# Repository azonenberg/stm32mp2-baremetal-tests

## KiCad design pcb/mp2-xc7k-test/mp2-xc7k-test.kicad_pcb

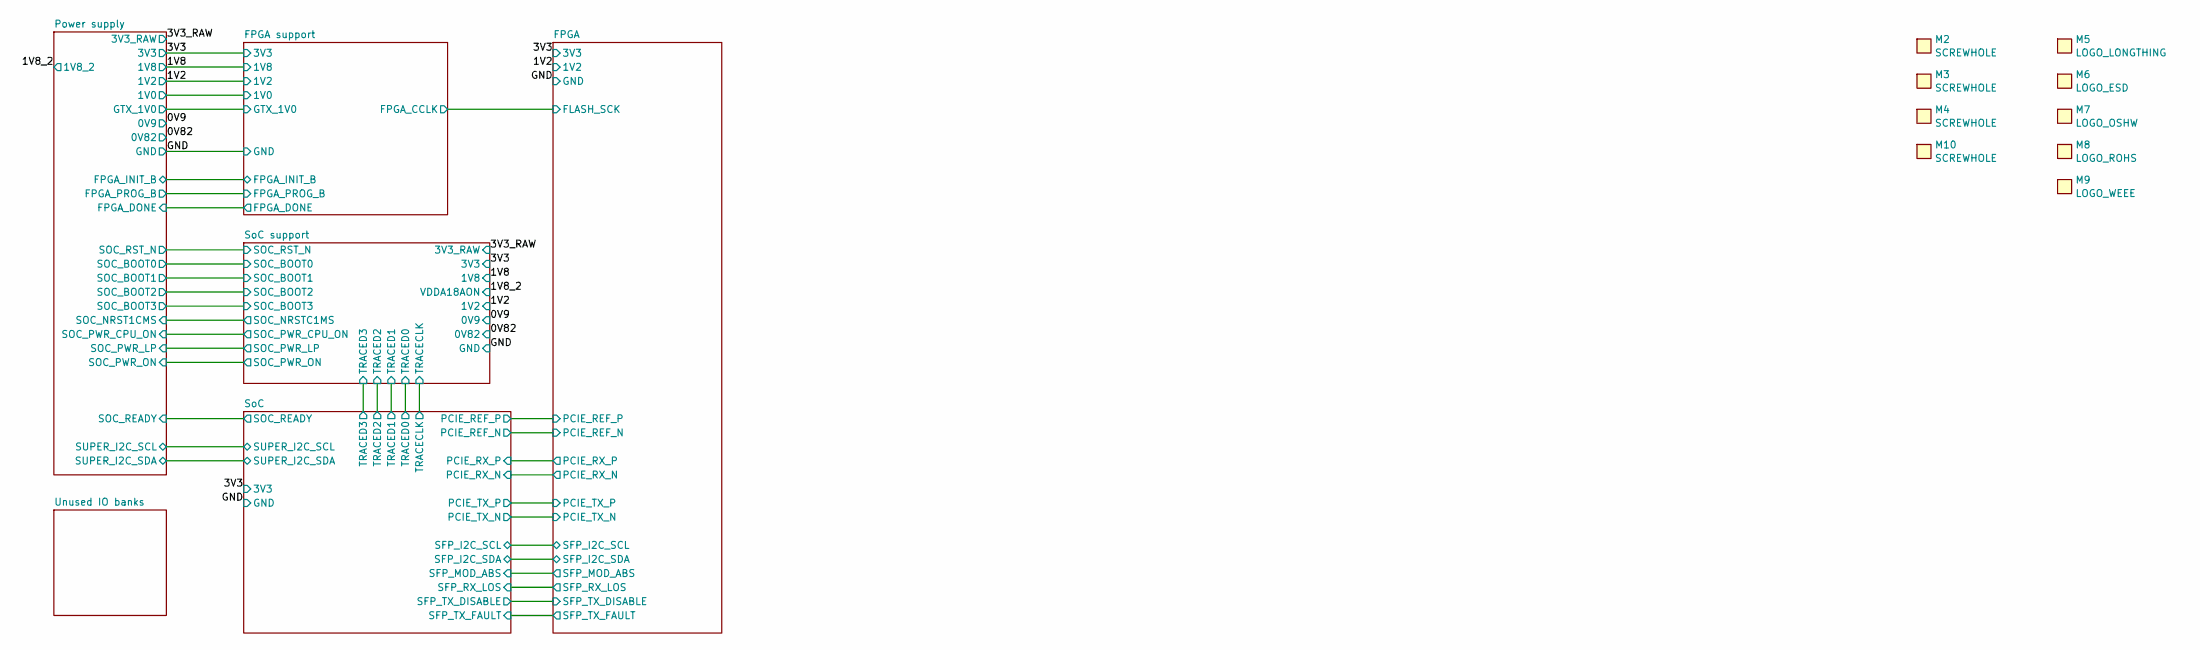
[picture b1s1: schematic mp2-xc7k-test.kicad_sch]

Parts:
M2, M3, M4, M10: SCREWHOLE; MECHANICAL_CLEARANCEHOLE_4_40
M5: LOGO_LONGTHING; LONGTHING-1200DPI
M6: LOGO_ESD; LOGO_ESD_SENSITIVE_7MM
M7: LOGO_OSHW; Logo_silk_OSHW_6x6mm
M8: LOGO_ROHS; Logo_silk_ROHS_5x2.8mm
M9: LOGO_WEEE; Logo_silk_WEEE_3.4x5mm

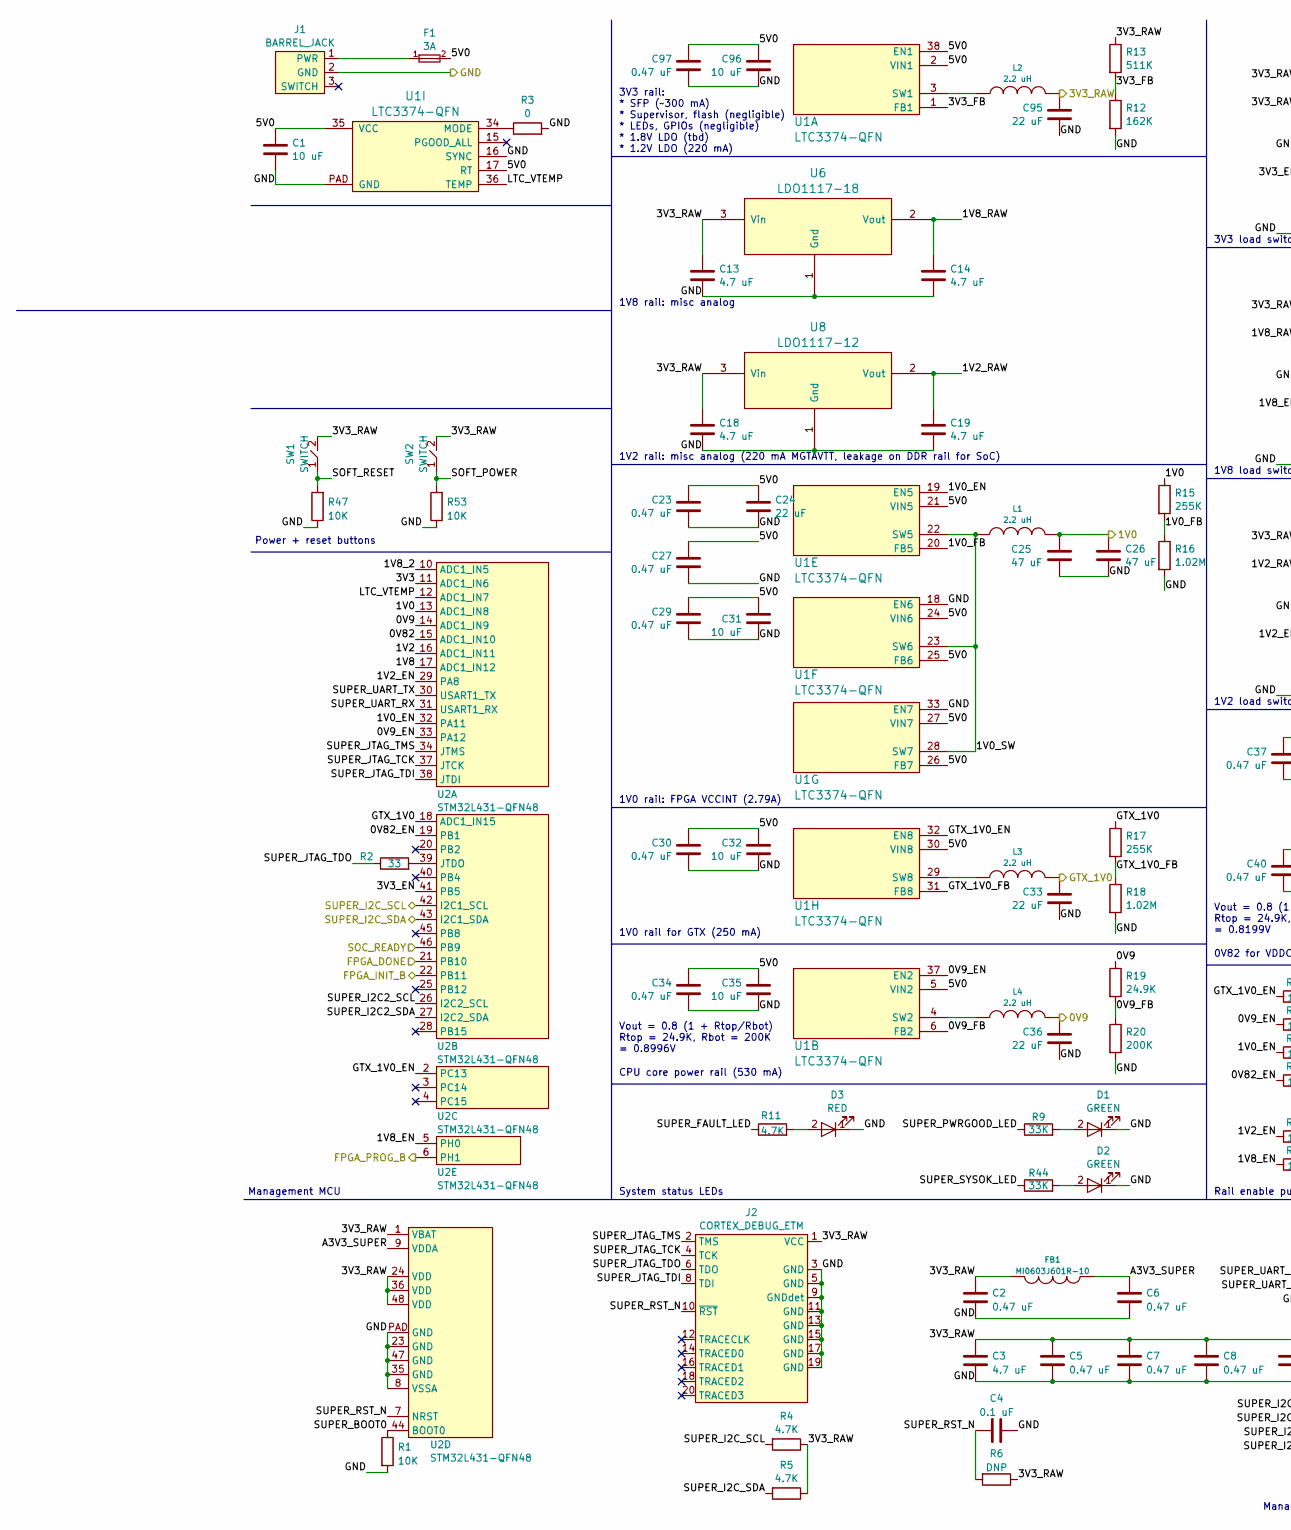
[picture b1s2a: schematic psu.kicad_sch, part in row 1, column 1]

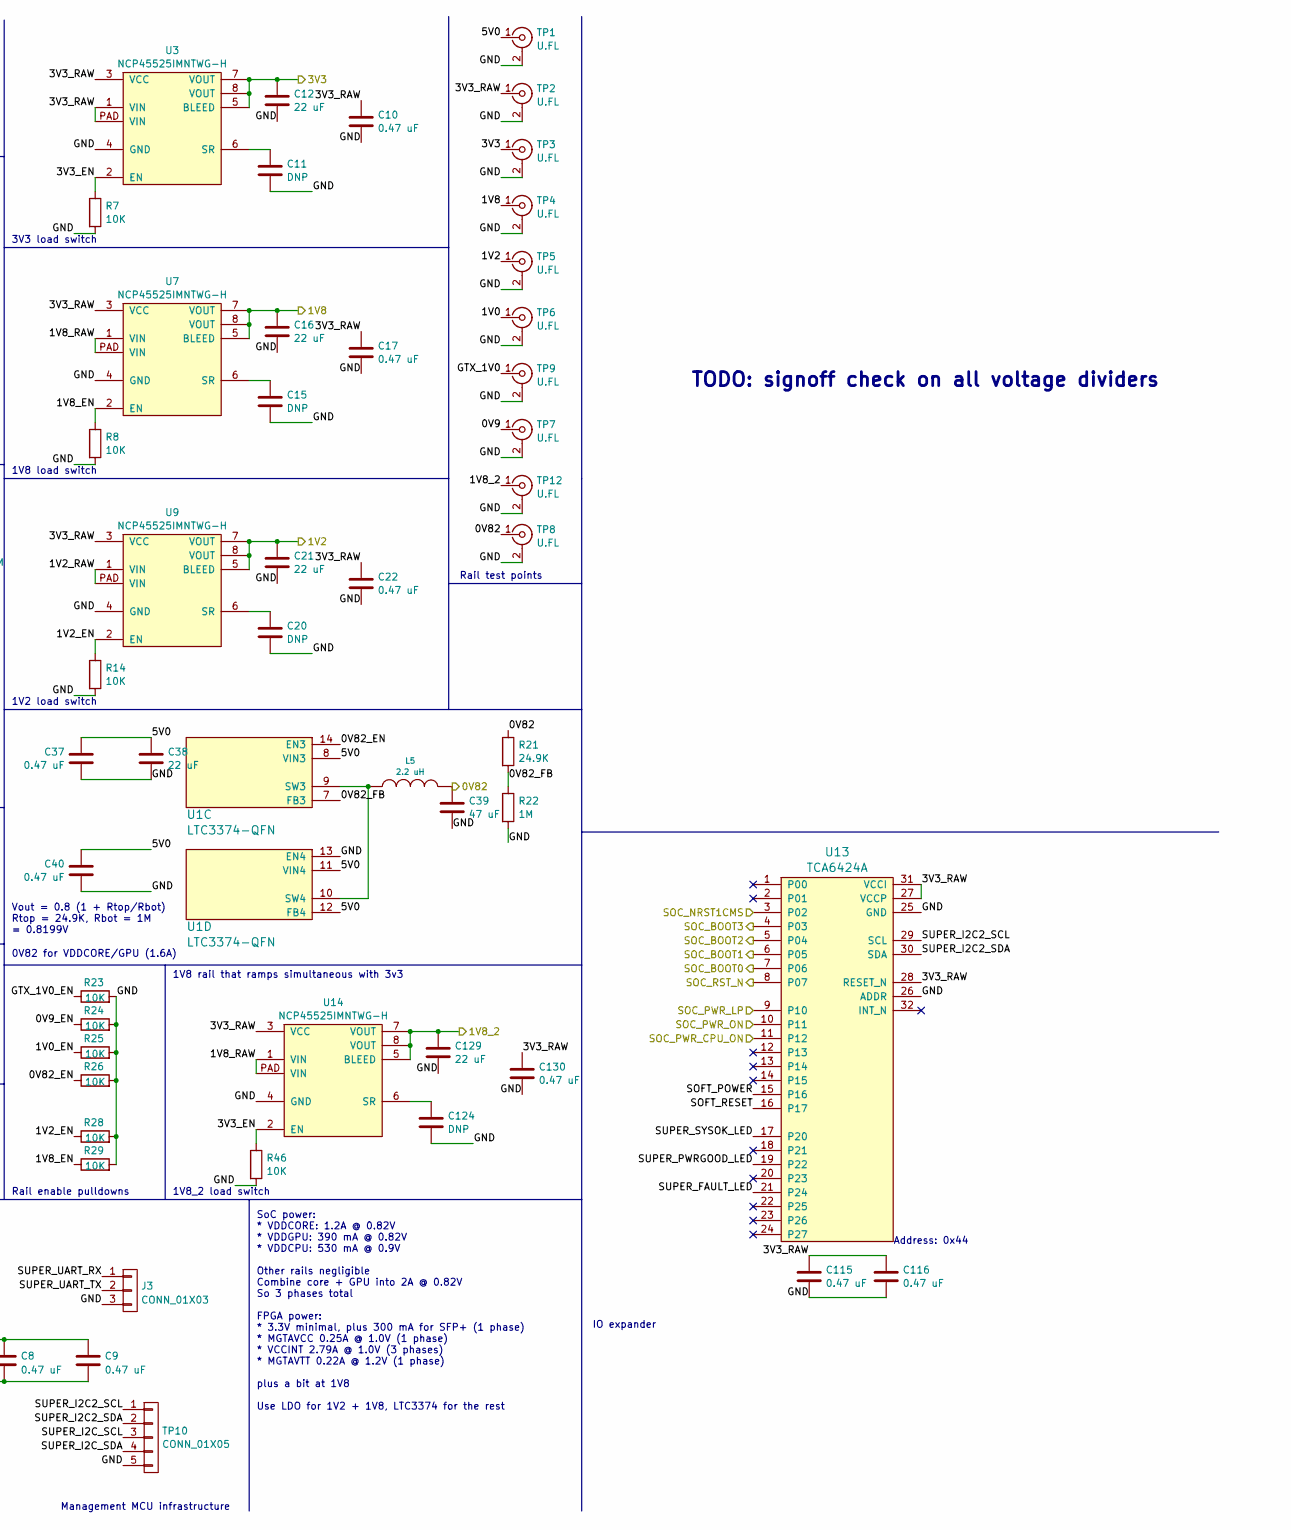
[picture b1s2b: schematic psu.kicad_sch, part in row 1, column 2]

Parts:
C1, C31, C32, C35, C96: 10 uF; EIA_1210_CAP_NOSILK
C2, C5, C6, C7, C8, C9, C10, C17, C22, C23, C27, C29, C30, C34, C37, C40, C97, C115, C116, C130: 0.47 uF; EIA_0402_CAP_NOSILK
C3, C13, C14, C18, C19: 4.7 uF; EIA_0603_CAP_NOSILK
C4: 0.1 uF; EIA_0402_CAP_NOSILK
C11, C15, C20, C124: DNP; EIA_0402_CAP_NOSILK
C12, C16, C21, C24, C38, C129: 22 uF; EIA_1210_CAP_NOSILK
C25, C26, C39: 47 uF; EIA_1206_CAP_NOSILK
C33, C36, C95: 22 uF; EIA_1206_CAP_NOSILK
D1, D2: GREEN; EIA_0402_LED
D3: RED; EIA_0402_LED
F1: 3A; EIA_0402_RES_NOSILK
FB1: MI0603J601R-10; EIA_0603_INDUCTOR_NOSILK
J1: BARREL_JACK; CONN_CUI_PJ-058BH_HIPWR_BARREL_NOSLOT
J2: CORTEX_DEBUG_ETM; CONN_HEADER_1.27MM_2x10_SMT_SAMTEC_FTSH-110-01-L-DV-K
J3: CONN_01X03; CONN_HEADER_2.54MM_1x3
L1, L2, L3, L4, L5: 2.2 uH; EIA_1210_CAP_NOSILK
R1, R7, R8, R14, R23, R24, R25, R26, R28, R29, R46, R47, R53: 10K; EIA_0402_RES_NOSILK
R2: 33; EIA_0402_RES_NOSILK
R3: 0; EIA_0402_RES_NOSILK
R4, R5, R11: 4.7K; EIA_0402_RES_NOSILK
R6: DNP; EIA_0402_RES_NOSILK
R9, R44: 33K; EIA_0402_RES_NOSILK
R12: 162K; EIA_0402_RES_NOSILK
R13: 511K; EIA_0402_RES_NOSILK
R15, R17: 255K; EIA_0402_RES_NOSILK
R16, R18: 1.02M; EIA_0402_RES_NOSILK
R19, R21: 24.9K; EIA_0402_RES_NOSILK
R20: 200K; EIA_0402_RES_NOSILK
R22: 1M; EIA_0402_RES_NOSILK
SW1, SW2: SWITCH; SWITCH_RAFI_MICON_5
TP1, TP2, TP3, TP4, TP5, TP6, TP7, TP8, TP9, TP12: U.FL; CONN_U.FL_TE_1909763-1
TP10: CONN_01X05; CONN_HEADER_2.54MM_1x5_REFLOW
U1: LTC3374-QFN; QFN_38_0.5MM_5x7MM
U2: STM32L431-QFN48; QFN_48_0.5MM_7x7MM
U3, U7, U9, U14: NCP45525IMNTWG-H; DFN_8_0.5MM_2x2MM
U6: LDO1117-18; SOT223-4
U8: LDO1117-12; SOT223-4
U13: TCA6424A; QFN_32_0.5MM_5x5MM

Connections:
/0V9: C36.1, L4.1, R19.1, TP7.1 (In), U2.14 (ADC1_IN9); also elsewhere on the board
/0V82: C39.1, L5.1, R21.1, TP8.1 (In), U2.15 (ADC1_IN10); also elsewhere on the board
/1V2: C21.1, TP5.1 (In), U2.16 (ADC1_IN11), U9.5 (BLEED), U9.7 (VOUT), U9.8 (VOUT); also elsewhere on the board
/1V8: C16.1, TP4.1 (In), U2.17 (ADC1_IN12), U7.5 (BLEED), U7.7 (VOUT), U7.8 (VOUT); also elsewhere on the board
/1V8_2: C129.1, TP12.1 (In), U2.10 (ADC1_IN5), U14.5 (BLEED), U14.7 (VOUT), U14.8 (VOUT); also elsewhere on the board
/3V3: C12.1, TP3.1 (In), U2.11 (ADC1_IN6), U3.5 (BLEED), U3.7 (VOUT), U3.8 (VOUT); also elsewhere on the board
/3V3_RAW: C2.1, C3.1, C5.1, C7.1, C8.1, C9.1, C10.1, C13.1, C17.1, C18.1, C22.1, C95.1, C115.1, C116.1, C130.1, FB1.2, J2.1 (VCC), L2.2, R4.1, R5.1, R6.1, R13.1, SW1.2, SW2.2, TP2.1 (In), U2.1 (VBAT), U2.24 (VDD), U2.36 (VDD), U2.48 (VDD), U3.1 (VIN), U3.3 (VCC), U3.PAD (VIN), U6.3 (Vin), U7.3 (VCC), U8.3 (Vin), U9.3 (VCC), U13.27 (VCCP), U13.28 (RESET_N), U13.31 (VCCI), U14.3 (VCC); also elsewhere on the board
/FPGA support/1V0: C25.1, C26.1, L1.1, R15.1, TP6.1 (In), U2.13 (ADC1_IN8); also elsewhere on the board
/FPGA support/FPGA_DONE: U2.21 (PB10); also elsewhere on the board
/FPGA support/FPGA_INIT_B: U2.22 (PB11); also elsewhere on the board
/FPGA support/FPGA_PROG_B: U2.6 (PH1); also elsewhere on the board
/FPGA support/GTX_1V0: C33.1, L3.1, R17.1, TP9.1 (In), U2.18 (ADC1_IN15); also elsewhere on the board
/GND: C1.2, C2.2, C3.2, C4.2, C5.2, C6.2, C7.2, C8.2, C9.2, C10.2, C11.2, C12.2, C13.2, C14.2, C15.2, C16.2, C17.2, C18.2, C19.2, C20.2, C21.2, C22.2, C23.2, C24.2, C25.2, C26.2, C27.2, C29.2, C30.2, C31.2, C32.2, C33.2, C34.2, C35.2, C36.2, C37.2, C38.2, C39.2, C40.2, C95.2, C96.2, C97.2, C115.2, C116.2, C124.2, C129.2, C130.2, D1.1 (K), D2.1 (K), D3.1 (K), J1.2 (GND), J2.3 (GND), J2.5 (GND), J2.9 (GNDdet), J2.11 (GND), J2.13 (GND), J2.15 (GND), J2.17 (GND), J2.19 (GND), J3.3, R1.2, R3.2, R7.2, R8.2, R12.2, R14.2, R16.2, R18.2, R20.2, R22.2, R23.2, R24.2, R25.2, R26.2, R28.2, R29.2, R46.2, R47.1, R53.1, TP1.2 (Ext), TP2.2 (Ext), TP3.2 (Ext), TP4.2 (Ext), TP5.2 (Ext), TP6.2 (Ext), TP7.2 (Ext), TP8.2 (Ext), TP9.2 (Ext), TP10.5, TP12.2 (Ext), U1.13 (EN4), U1.16 (SYNC), U1.18 (EN6), U1.33 (EN7), U1.PAD (GND), U2.8 (VSSA), U2.23 (GND), U2.35 (GND), U2.47 (GND), U2.PAD (GND), U3.4 (GND), U6.1 (Gnd), U7.4 (GND), U8.1 (Gnd), U9.4 (GND), U13.25 (GND), U13.26 (ADDR), U14.4 (GND); also elsewhere on the board
/Power supply/0V9_EN: R24.1, U1.37 (EN2), U2.33 (PA12)
/Power supply/0V9_FB: R19.2, R20.1, U1.6 (FB2)
/Power supply/0V82_EN: R26.1, U1.14 (EN3), U2.19 (PB1)
/Power supply/0V82_FB: R21.2, R22.1, U1.7 (FB3)
/Power supply/1V0_EN: R25.1, U1.19 (EN5), U2.32 (PA11)
/Power supply/1V0_FB: R15.2, R16.1, U1.20 (FB5)
/Power supply/1V0_SW: L1.2, U1.22 (SW5), U1.23 (SW6), U1.28 (SW7)
/Power supply/1V2_EN: R14.1, R28.1, U2.29 (PA8), U9.2 (EN)
/Power supply/1V2_RAW: C19.1, U8.2 (Vout), U9.1 (VIN), U9.PAD (VIN)
/Power supply/1V8_EN: R8.1, R29.1, U2.5 (PH0), U7.2 (EN)
/Power supply/1V8_RAW: C14.1, U6.2 (Vout), U7.1 (VIN), U7.PAD (VIN), U14.1 (VIN), U14.PAD (VIN)
/Power supply/3V3_EN: R7.1, R46.1, U2.41 (PB5), U3.2 (EN), U14.2 (EN)
/Power supply/3V3_FB: R12.1, R13.2, U1.1 (FB1)
/Power supply/5V0: C1.1, C23.1, C24.1, C27.1, C29.1, C30.1, C31.1, C32.1, C34.1, C35.1, C37.1, C38.1, C40.1, C96.1, C97.1, F1.2, TP1.1 (In), U1.2 (VIN1), U1.5 (VIN2), U1.8 (VIN3), U1.11 (VIN4), U1.12 (FB4), U1.17 (RT), U1.21 (VIN5), U1.24 (VIN6), U1.25 (FB6), U1.26 (FB7), U1.27 (VIN7), U1.30 (VIN8), U1.35 (VCC), U1.38 (EN1)
/Power supply/A3V3_SUPER: C6.1, FB1.1, U2.9 (VDDA)
/Power supply/GTX_1V0_EN: R23.1, U1.32 (EN8), U2.2 (PC13)
/Power supply/GTX_1V0_FB: R17.2, R18.1, U1.31 (FB8)
/Power supply/LTC_VTEMP: U1.36 (TEMP), U2.12 (ADC1_IN7)
/Power supply/SOC_BOOT0: U13.7 (P06); also elsewhere on the board
/Power supply/SOC_BOOT1: U13.6 (P05); also elsewhere on the board
/Power supply/SOC_BOOT2: U13.5 (P04); also elsewhere on the board
/Power supply/SOC_BOOT3: U13.4 (P03); also elsewhere on the board
/Power supply/SOC_NRST1CMS: U13.3 (P02); also elsewhere on the board
/Power supply/SOC_PWR_CPU_ON: U13.11 (P12); also elsewhere on the board
/Power supply/SOC_PWR_LP: U13.9 (P10); also elsewhere on the board
/Power supply/SOC_PWR_ON: U13.10 (P11); also elsewhere on the board
/Power supply/SOC_READY: U2.46 (PB9); also elsewhere on the board
/Power supply/SOFT_POWER: R53.2, SW2.1, U13.15 (P16)
/Power supply/SOFT_RESET: R47.2, SW1.1, U13.16 (P17)
/Power supply/SUPER_BOOT0: R1.1, U2.44 (BOOT0)
/Power supply/SUPER_FAULT_LED: R11.1, U13.21 (P24)
/Power supply/SUPER_I2C2_SCL: TP10.1, U2.26 (I2C2_SCL), U13.29 (SCL)
/Power supply/SUPER_I2C2_SDA: TP10.2, U2.27 (I2C2_SDA), U13.30 (SDA)
/Power supply/SUPER_I2C_SCL: R4.2, TP10.3, U2.42 (I2C1_SCL); also elsewhere on the board
/Power supply/SUPER_I2C_SDA: R5.2, TP10.4, U2.43 (I2C1_SDA); also elsewhere on the board
/Power supply/SUPER_JTAG_TCK: J2.4 (TCK), U2.37 (JTCK)
/Power supply/SUPER_JTAG_TDI: J2.8 (TDI), U2.38 (JTDI)
/Power supply/SUPER_JTAG_TDO: J2.6 (TDO), R2.1
/Power supply/SUPER_JTAG_TMS: J2.2 (TMS), U2.34 (JTMS)
/Power supply/SUPER_PWRGOOD_LED: R9.1, U13.19 (P22)
/Power supply/SUPER_RST_N: C4.1, J2.10 (~RST), R6.2, U2.7 (NRST)
/Power supply/SUPER_SYSOK_LED: R44.1, U13.17 (P20)
/Power supply/SUPER_UART_RX: J3.1, U2.31 (USART1_RX)
/Power supply/SUPER_UART_TX: J3.2, U2.30 (USART1_TX)
/SoC support/SOC_RST_N: U13.8 (P07); also elsewhere on the board
unnamed: D1.2 (A), R9.2
unnamed: D2.2 (A), R44.2
unnamed: D3.2 (A), R11.2
unnamed: F1.1, J1.1 (PWR)
unnamed: L2.1, U1.3 (SW1)
unnamed: L4.2, U1.4 (SW2)
unnamed: L5.2, U1.9 (SW3), U1.10 (SW4)
unnamed: L3.2, U1.29 (SW8)
unnamed: R3.1, U1.34 (MODE)
unnamed: R2.2, U2.39 (JTDO)
unnamed: C11.1, U3.6 (SR)
unnamed: C15.1, U7.6 (SR)
unnamed: C20.1, U9.6 (SR)
unnamed: C124.1, U14.6 (SR)

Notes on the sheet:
Address: 0x44
1V0 rail for GTX (250 mA)
1V2 load switch
Rail test points
1V8 rail: misc analog
1V8_2 load switch
Management MCU
System status LEDs
3V3 rail: * SFP (~300 mA) * Supervisor, flash (negligible) * LEDs, GPIOs (negligible) * 1.8V LDO (tbd) * 1.2V LDO (220 mA)
Vout = 0.8 (1 + Rtop/Rbot) Rtop = 24.9K, Rbot = 1M = 0.8199V
3V3 load switch
Management MCU infrastructure
IO expander
1V0 rail: FPGA VCCINT (2.79A)
TODO: signoff check on all voltage dividers
Rail enable pulldowns
1V8 rail that ramps simultaneous with 3v3
Vout = 0.8 (1 + Rtop/Rbot) Rtop = 24.9K, Rbot = 200K = 0.8996V
SoC power: * VDDCORE: 1.2A @ 0.82V * VDDGPU: 390 mA @ 0.82V * VDDCPU: 530 mA @ 0.9V Other rails negligible Combine core + GPU into 2A @ 0.82V So 3 phases total FPGA power: * 3.3V minimal, plus 300 mA for SFP+ (1 phase) * MGTAVCC 0.25A @ 1.0V (1 phase) * VCCINT 2.79A @ 1.0V (3 phases) * MGTAVTT 0.22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
1V2 rail: misc analog (220 mA MGTAVTT, leakage on DDR rail for SoC)
0V82 for VDDCORE/GPU (1.6A)
CPU core power rail (530 mA)
Power + reset buttons
1V8 load switch

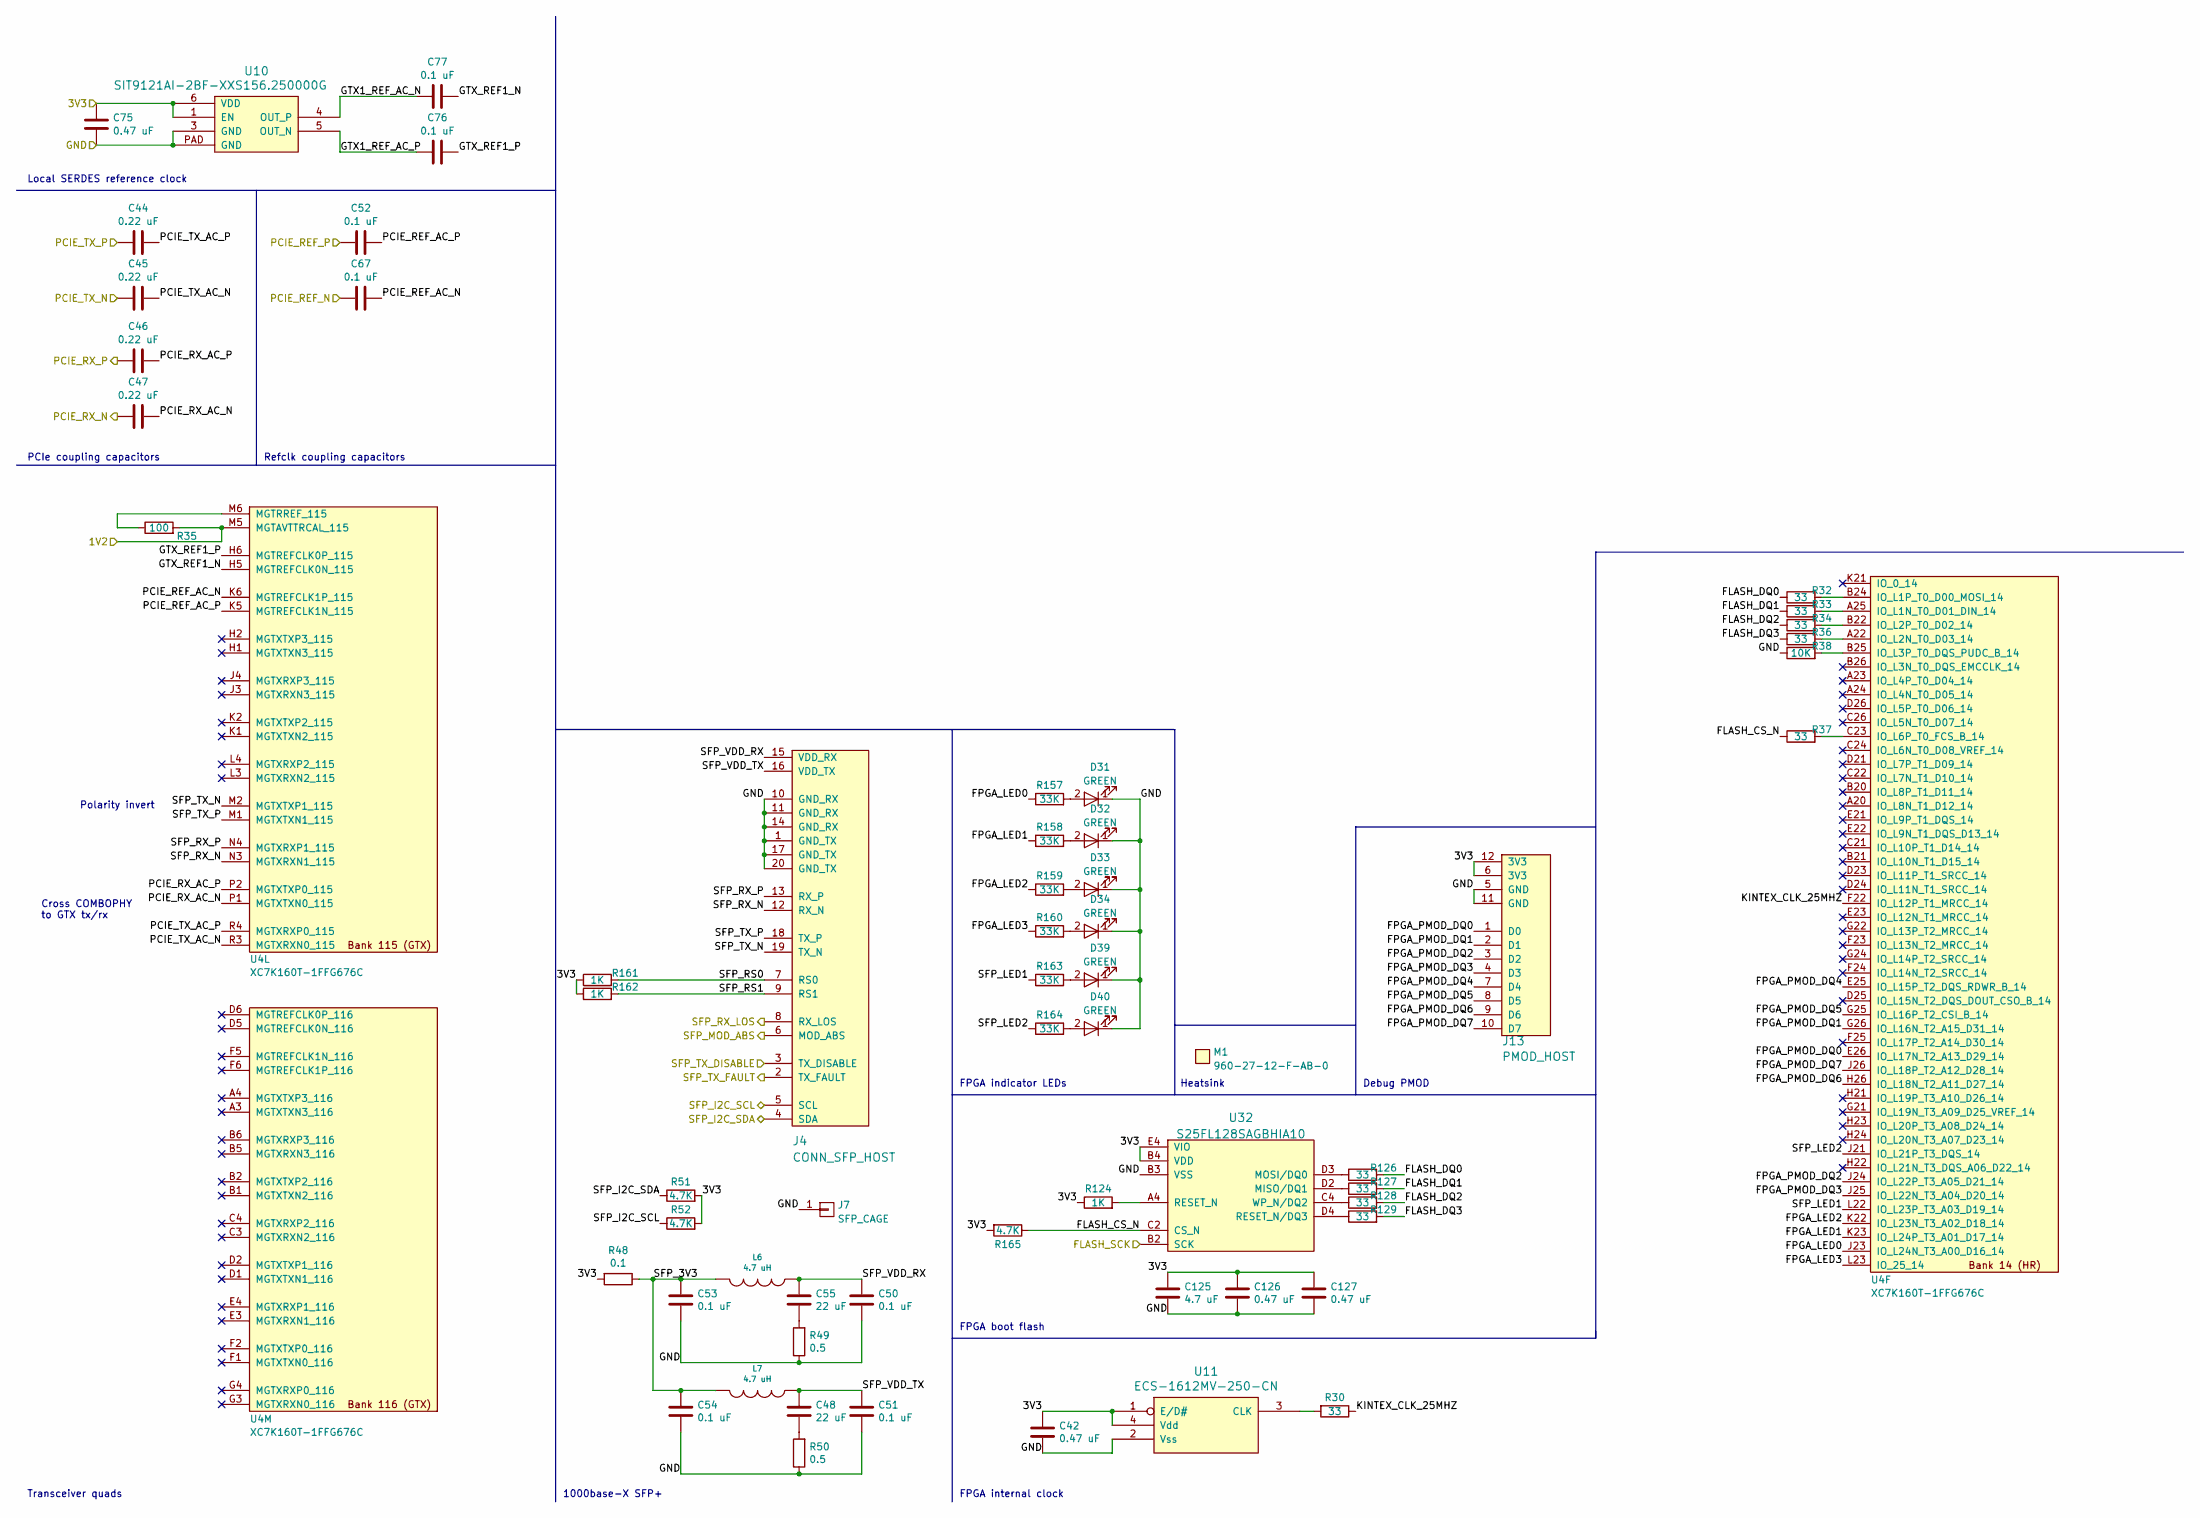
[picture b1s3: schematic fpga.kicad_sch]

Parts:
C42, C75, C126, C127: 0.47 uF; EIA_0402_CAP_NOSILK
C44, C45, C46, C47: 0.22 uF; EIA_0402_CAP_NOSILK
C48, C55: 22 uF; EIA_0805_CAP_NOSILK
C50, C51, C52, C53, C54, C67, C76, C77: 0.1 uF; EIA_0402_CAP_NOSILK
C125: 4.7 uF; EIA_0603_CAP_NOSILK
D31, D32, D33, D34, D39, D40: GREEN; EIA_0402_LED
J4: CONN_SFP_HOST; CONN_SFP+_AMPHENOL_UE76_A10_2000T
J7: SFP_CAGE; CONN_SFP_CAGE_TE_2007194-1
J13: PMOD_HOST; CONN_HEADER_2.54MM_2x6_RA_PMOD_HOST
L6, L7: 4.7 uH; EIA_0805_INDUCTOR_NOSILK
M1: 960-27-12-F-AB-0; HEATSINK_WAKEFIELDVETTE_960-27-12-D-AB-0
R30, R32, R33, R34, R36, R37, R126, R127, R128, R129: 33; EIA_0402_RES_NOSILK
R35: 100; EIA_0402_RES_NOSILK
R38: 10K; EIA_0402_RES_NOSILK
R48: 0.1; EIA_0402_RES_NOSILK
R49, R50: 0.5; EIA_0402_RES_NOSILK
R51, R52, R165: 4.7K; EIA_0402_RES_NOSILK
R124, R161, R162: 1K; EIA_0402_RES_NOSILK
R157, R158, R159, R160, R163, R164: 33K; EIA_0402_RES_NOSILK
U4: XC7K160T-1FFG676C; BGA_676_27x27_FULLARRAY_1MM_FFG676
U10: SIT9121AI-2BF-XXS156.250000G; OSCILLATOR_LVDS_3.2x2.5
U11: ECS-1612MV-250-CN; OSCILLATOR_1.6x1.2
U32: S25FL128SAGBHIA10; BGA_24_6x8_DEPOP1_1MM

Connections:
/1V2: R35.2, U4.M5 (MGTAVTTRCAL_115); also elsewhere on the board
/3V3: C42.1, C75.1, C125.1, C126.1, C127.1, J13.6 (3V3), J13.12 (3V3), R48.2, R51.2, R52.2, R124.1, R161.1, R162.1, R165.2, U10.1 (EN), U10.6 (VDD), U11.1 (E/D#), U11.4 (Vdd), U32.B4 (VDD), U32.E4 (VIO); also elsewhere on the board
/FPGA support/FPGA_CCLK: U32.B2 (SCK); also elsewhere on the board
/FPGA/FLASH_CS_N: R37.1, R165.1, U32.C2 (CS_N)
/FPGA/FLASH_DQ0: R32.1, R126.2
/FPGA/FLASH_DQ1: R33.1, R127.2
/FPGA/FLASH_DQ2: R34.1, R128.2
/FPGA/FLASH_DQ3: R36.1, R129.2
/FPGA/FPGA_LED0: R157.1, U4.J23 (IO_L24N_T3_A00_D16_14)
/FPGA/FPGA_LED1: R158.1, U4.K23 (IO_L24P_T3_A01_D17_14)
/FPGA/FPGA_LED2: R159.1, U4.K22 (IO_L23N_T3_A02_D18_14)
/FPGA/FPGA_LED3: R160.1, U4.L23 (IO_25_14)
/FPGA/FPGA_PMOD_DQ0: J13.1 (D0), U4.E26 (IO_L17N_T2_A13_D29_14)
/FPGA/FPGA_PMOD_DQ1: J13.2 (D1), U4.G26 (IO_L16N_T2_A15_D31_14)
/FPGA/FPGA_PMOD_DQ2: J13.3 (D2), U4.J24 (IO_L22P_T3_A05_D21_14)
/FPGA/FPGA_PMOD_DQ3: J13.4 (D3), U4.J25 (IO_L22N_T3_A04_D20_14)
/FPGA/FPGA_PMOD_DQ4: J13.7 (D4), U4.E25 (IO_L15P_T2_DQS_RDWR_B_14)
/FPGA/FPGA_PMOD_DQ5: J13.8 (D5), U4.G25 (IO_L16P_T2_CSI_B_14)
/FPGA/FPGA_PMOD_DQ6: J13.9 (D6), U4.H26 (IO_L18N_T2_A11_D27_14)
/FPGA/FPGA_PMOD_DQ7: J13.10 (D7), U4.J26 (IO_L18P_T2_A12_D28_14)
/FPGA/GTX1_REF_AC_N: C77.1, U10.4 (OUT_P)
/FPGA/GTX1_REF_AC_P: C76.1, U10.5 (OUT_N)
/FPGA/GTX_REF1_N: C77.2, U4.H5 (MGTREFCLK0N_115)
/FPGA/GTX_REF1_P: C76.2, U4.H6 (MGTREFCLK0P_115)
/FPGA/KINTEX_CLK_25MHZ: R30.1, U4.F22 (IO_L12P_T1_MRCC_14)
/FPGA/PCIE_REF_AC_N: C67.2, U4.K6 (MGTREFCLK1P_115)
/FPGA/PCIE_REF_AC_P: C52.2, U4.K5 (MGTREFCLK1N_115)
/FPGA/PCIE_REF_N: C67.1; also elsewhere on the board
/FPGA/PCIE_REF_P: C52.1; also elsewhere on the board
/FPGA/PCIE_RX_AC_N: C47.2, U4.P1 (MGTXTXN0_115)
/FPGA/PCIE_RX_AC_P: C46.2, U4.P2 (MGTXTXP0_115)
/FPGA/PCIE_RX_N: C47.1; also elsewhere on the board
/FPGA/PCIE_RX_P: C46.1; also elsewhere on the board
/FPGA/PCIE_TX_AC_N: C45.2, U4.R3 (MGTXRXN0_115)
/FPGA/PCIE_TX_AC_P: C44.2, U4.R4 (MGTXRXP0_115)
/FPGA/PCIE_TX_N: C45.1; also elsewhere on the board
/FPGA/PCIE_TX_P: C44.1; also elsewhere on the board
/FPGA/SFP_3V3: C53.1, C54.1, L6.2, L7.2, R48.1
/FPGA/SFP_I2C_SCL: J4.5 (SCL), R52.1; also elsewhere on the board
/FPGA/SFP_I2C_SDA: J4.4 (SDA), R51.1; also elsewhere on the board
/FPGA/SFP_LED1: R163.1, U4.L22 (IO_L23P_T3_A03_D19_14)
/FPGA/SFP_LED2: R164.1, U4.J21 (IO_L21P_T3_DQS_14)
/FPGA/SFP_MOD_ABS: J4.6 (MOD_ABS); also elsewhere on the board
/FPGA/SFP_RS0: J4.7 (RS0), R161.2
/FPGA/SFP_RS1: J4.9 (RS1), R162.2
/FPGA/SFP_RX_LOS: J4.8 (RX_LOS); also elsewhere on the board
/FPGA/SFP_RX_N: J4.12 (RX_N), U4.N3 (MGTXRXN1_115)
/FPGA/SFP_RX_P: J4.13 (RX_P), U4.N4 (MGTXRXP1_115)
/FPGA/SFP_TX_DISABLE: J4.3 (TX_DISABLE); also elsewhere on the board
/FPGA/SFP_TX_FAULT: J4.2 (TX_FAULT); also elsewhere on the board
/FPGA/SFP_TX_N: J4.19 (TX_N), U4.M2 (MGTXTXP1_115)
/FPGA/SFP_TX_P: J4.18 (TX_P), U4.M1 (MGTXTXN1_115)
/FPGA/SFP_VDD_RX: C50.1, C55.1, J4.15 (VDD_RX), L6.1
/FPGA/SFP_VDD_TX: C48.1, C51.1, J4.16 (VDD_TX), L7.1
/GND: C42.2, C50.2, C51.2, C53.2, C54.2, C75.2, C125.2, C126.2, C127.2, D31.1 (K), D32.1 (K), D33.1 (K), D34.1 (K), D39.1 (K), D40.1 (K), J4.1 (GND_TX), J4.10 (GND_RX), J4.11 (GND_RX), J4.14 (GND_RX), J4.17 (GND_TX), J4.20 (GND_TX), J7.1, J13.5 (GND), J13.11 (GND), R38.1, R49.1, R50.1, U10.3 (GND), U10.PAD (GND), U11.2 (Vss), U32.B3 (VSS); also elsewhere on the board
unnamed: C48.2, R50.2
unnamed: C55.2, R49.2
unnamed: D31.2 (A), R157.2
unnamed: D32.2 (A), R158.2
unnamed: D33.2 (A), R159.2
unnamed: D34.2 (A), R160.2
unnamed: D39.2 (A), R163.2
unnamed: D40.2 (A), R164.2
unnamed: R33.2, U4.A25 (IO_L1N_T0_D01_DIN_14)
unnamed: R32.2, U4.B24 (IO_L1P_T0_D00_MOSI_14)
unnamed: R36.2, U4.A22 (IO_L2N_T0_D03_14)
unnamed: R34.2, U4.B22 (IO_L2P_T0_D02_14)
unnamed: R38.2, U4.B25 (IO_L3P_T0_DQS_PUDC_B_14)
unnamed: R37.2, U4.C23 (IO_L6P_T0_FCS_B_14)
unnamed: R35.1, U4.M6 (MGTRREF_115)
unnamed: R30.2, U11.3 (CLK)
unnamed: R127.1, U32.D2 (MISO/DQ1)
unnamed: R126.1, U32.D3 (MOSI/DQ0)
unnamed: R124.2, U32.A4 (RESET_N)
unnamed: R129.1, U32.D4 (RESET_N/DQ3)
unnamed: R128.1, U32.C4 (WP_N/DQ2)

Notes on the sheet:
Polarity invert
Refclk coupling capacitors
PCIe coupling capacitors
Debug PMOD
FPGA indicator LEDs
Transceiver quads
FPGA internal clock
FPGA boot flash
1000base-X SFP+
Cross COMBOPHY to GTX tx/rx
Local SERDES reference clock
Heatsink

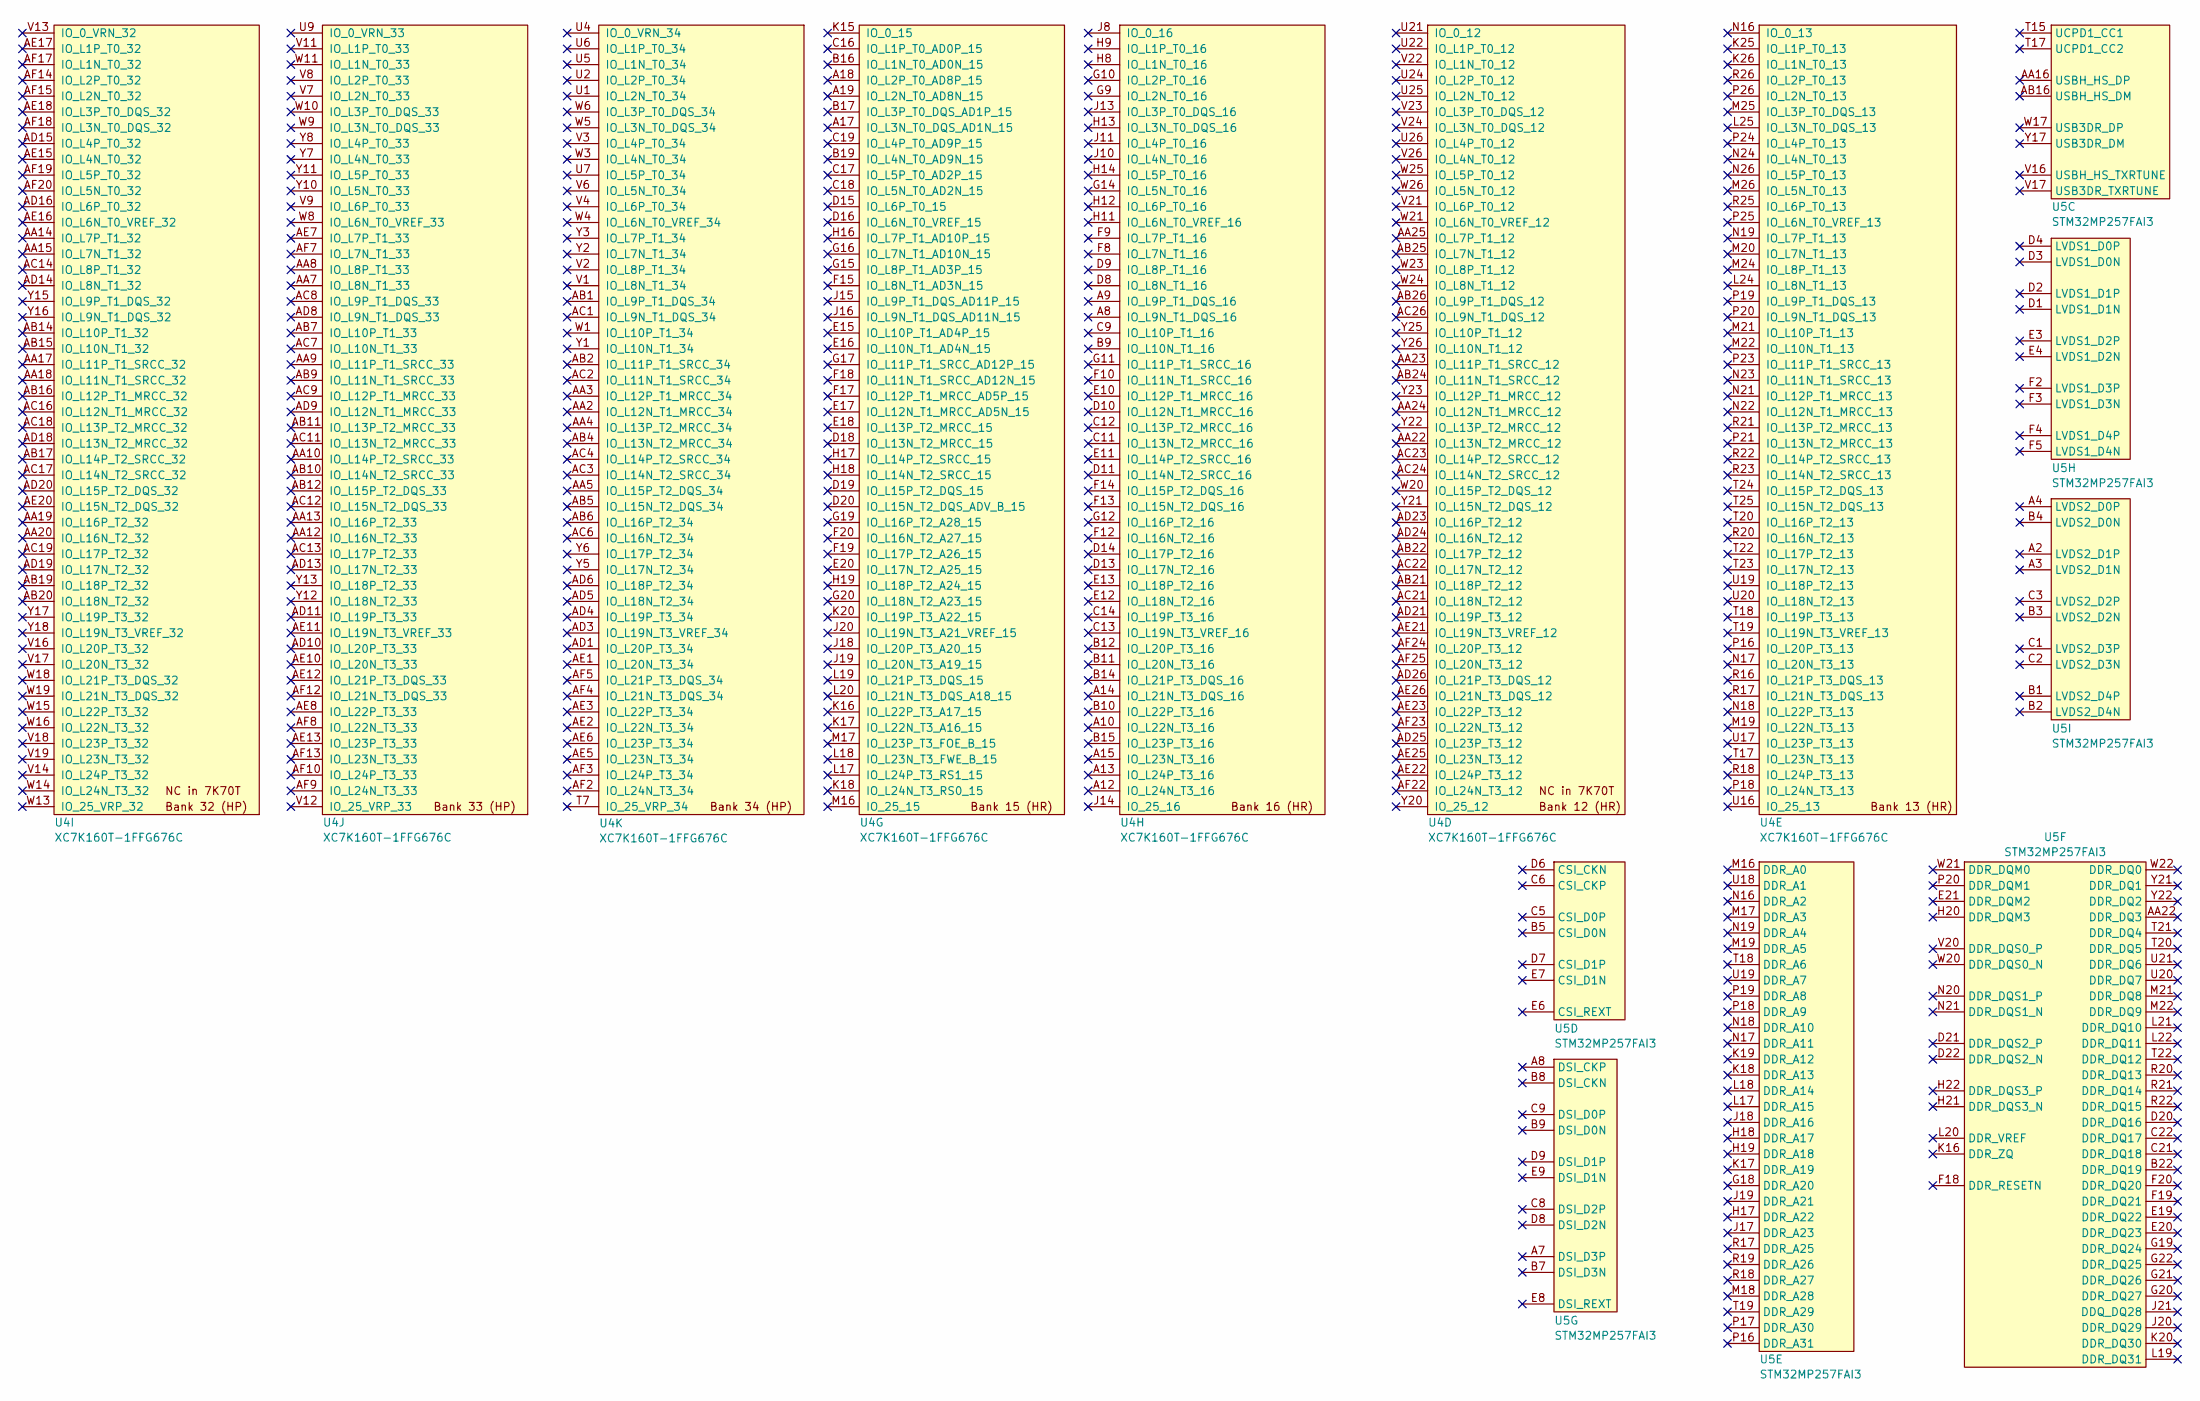
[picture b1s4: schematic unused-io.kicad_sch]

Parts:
U4: XC7K160T-1FFG676C; BGA_676_27x27_FULLARRAY_1MM_FFG676
U5: STM32MP257FAI3; BGA_436_18x18_DEPOP_0.8MM
